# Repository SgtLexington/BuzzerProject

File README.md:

# BuzzerProject

This is the buzzer project. 

## Building

## Testing

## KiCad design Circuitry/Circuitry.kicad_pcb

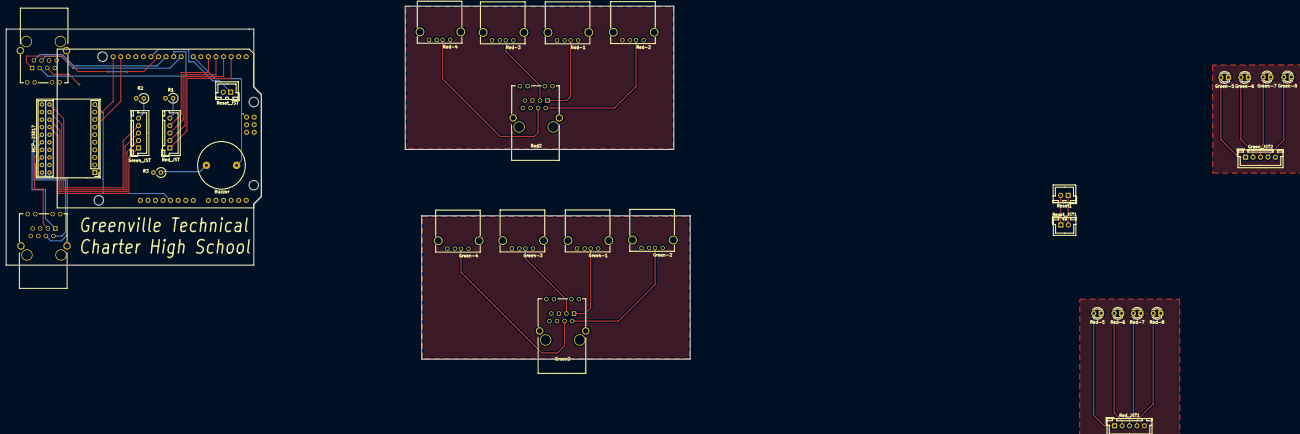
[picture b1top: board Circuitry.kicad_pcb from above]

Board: 2 copper layers, 33 parts (0 on the bottom side), 47 nets.

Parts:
ARD1: Arduino_Uno_Shield
Buzzer: Buzzer; BUZZER
Green2: RJ45; RJ45_TRANSFO
Green-1, Green-2, Green-3, Green-4: USB_A
Green-5, Green-6, Green-7, Green-8: LED; LED_D3.0mm
Green_JST, Green_JST2: Conn_01x05; JST_XH_B05B-XH-A_05x2.50mm_Straight
Green_RJ45: RJ45; RJ45_TRANSFO
MCP-23017: MCP23017; MCP-23017_Serial_Interface_2.54mmPitch_3x10
R1, R2, R3: R; R_Axial_DIN0309_L9.0mm_D3.2mm_P2.54mm_Vertical
Red2: RJ45; RJ45_TRANSFO
Red-1, Red-2, Red-3, Red-4: USB_A
Red-5, Red-6, Red-7, Red-8: LED; LED_D3.0mm
Red_JST, Red_JST1: Conn_01x05; JST_XH_B05B-XH-A_05x2.50mm_Straight
Red_RJ45: RJ45; RJ45_TRANSFO
Reset1: SW_Push; JST_XH_B02B-XH-A_02x2.50mm_Straight
Reset_JST, Reset_JST1: Conn_01x02; JST_XH_B02B-XH-A_02x2.50mm_Straight

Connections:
BTN_RESET: ARD1.D12, Reset_JST.1
BUZZER: ARD1.D7, Buzzer.1
CLOCK: ARD1.SCL, MCP-23017.12
DATA: ARD1.SDA, MCP-23017.13
GND: ARD1.GND1, Green_RJ45.5, MCP-23017.10, MCP-23017.15, MCP-23017.16, MCP-23017.17, R1.2, R2.2, R3.2, Red_RJ45.5, Reset_JST.2
G_BTN_1: Green_RJ45.4, MCP-23017.21
G_BTN_2: Green_RJ45.3, MCP-23017.22
G_BTN_3: Green_RJ45.2, MCP-23017.23
G_BTN_4: Green_RJ45.1, MCP-23017.24
G_LED_1: Green_JST.1, MCP-23017.5
G_LED_2: Green_JST.2, MCP-23017.6
G_LED_3: Green_JST.3, MCP-23017.7
G_LED_4: Green_JST.4, MCP-23017.8
unnamed: R1.1, Red_JST.5
unnamed: Green_JST.5, R2.1
unnamed: Buzzer.2, R3.1
unnamed: ARD1.5V1, MCP-23017.9
unnamed: Green2.1, Green-1.2
unnamed: Green2.5, Green-1.4, Green-2.4, Green-3.4, Green-4.4
unnamed: Green2.2, Green-2.2
unnamed: Green2.3, Green-3.2
unnamed: Green2.4, Green-4.2
unnamed: Green-5.1, Green-6.1, Green-7.1, Green-8.1, Green_JST2.5
unnamed: Green-5.2, Green_JST2.1
unnamed: Green-6.2, Green_JST2.2
unnamed: Green-7.2, Green_JST2.3
unnamed: Green-8.2, Green_JST2.4
unnamed: Red2.1, Red-1.2
unnamed: Red2.5, Red-1.4, Red-2.4, Red-3.4, Red-4.4
unnamed: Red2.2, Red-2.2
unnamed: Red2.3, Red-3.2
unnamed: Red2.4, Red-4.2
unnamed: Red-5.1, Red-6.1, Red-7.1, Red-8.1, Red_JST1.5
unnamed: Red-5.2, Red_JST1.1
unnamed: Red-6.2, Red_JST1.2
unnamed: Red-7.2, Red_JST1.3
unnamed: Red-8.2, Red_JST1.4
unnamed: Reset1.1, Reset_JST1.2
unnamed: Reset1.2, Reset_JST1.1
R_BTN_1: ARD1.D8, Red_RJ45.4
R_BTN_2: ARD1.D9, Red_RJ45.3
R_BTN_3: ARD1.D10, Red_RJ45.2
R_BTN_4: ARD1.D11, Red_RJ45.1
R_LED_1: ARD1.D2, Red_JST.1
R_LED_2: ARD1.D3, Red_JST.2
R_LED_3: ARD1.D4, Red_JST.3
R_LED_4: ARD1.D5, Red_JST.4

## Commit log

2018-08-11 Initial version
2018-08-13 this adds an image so you can see how to do it
